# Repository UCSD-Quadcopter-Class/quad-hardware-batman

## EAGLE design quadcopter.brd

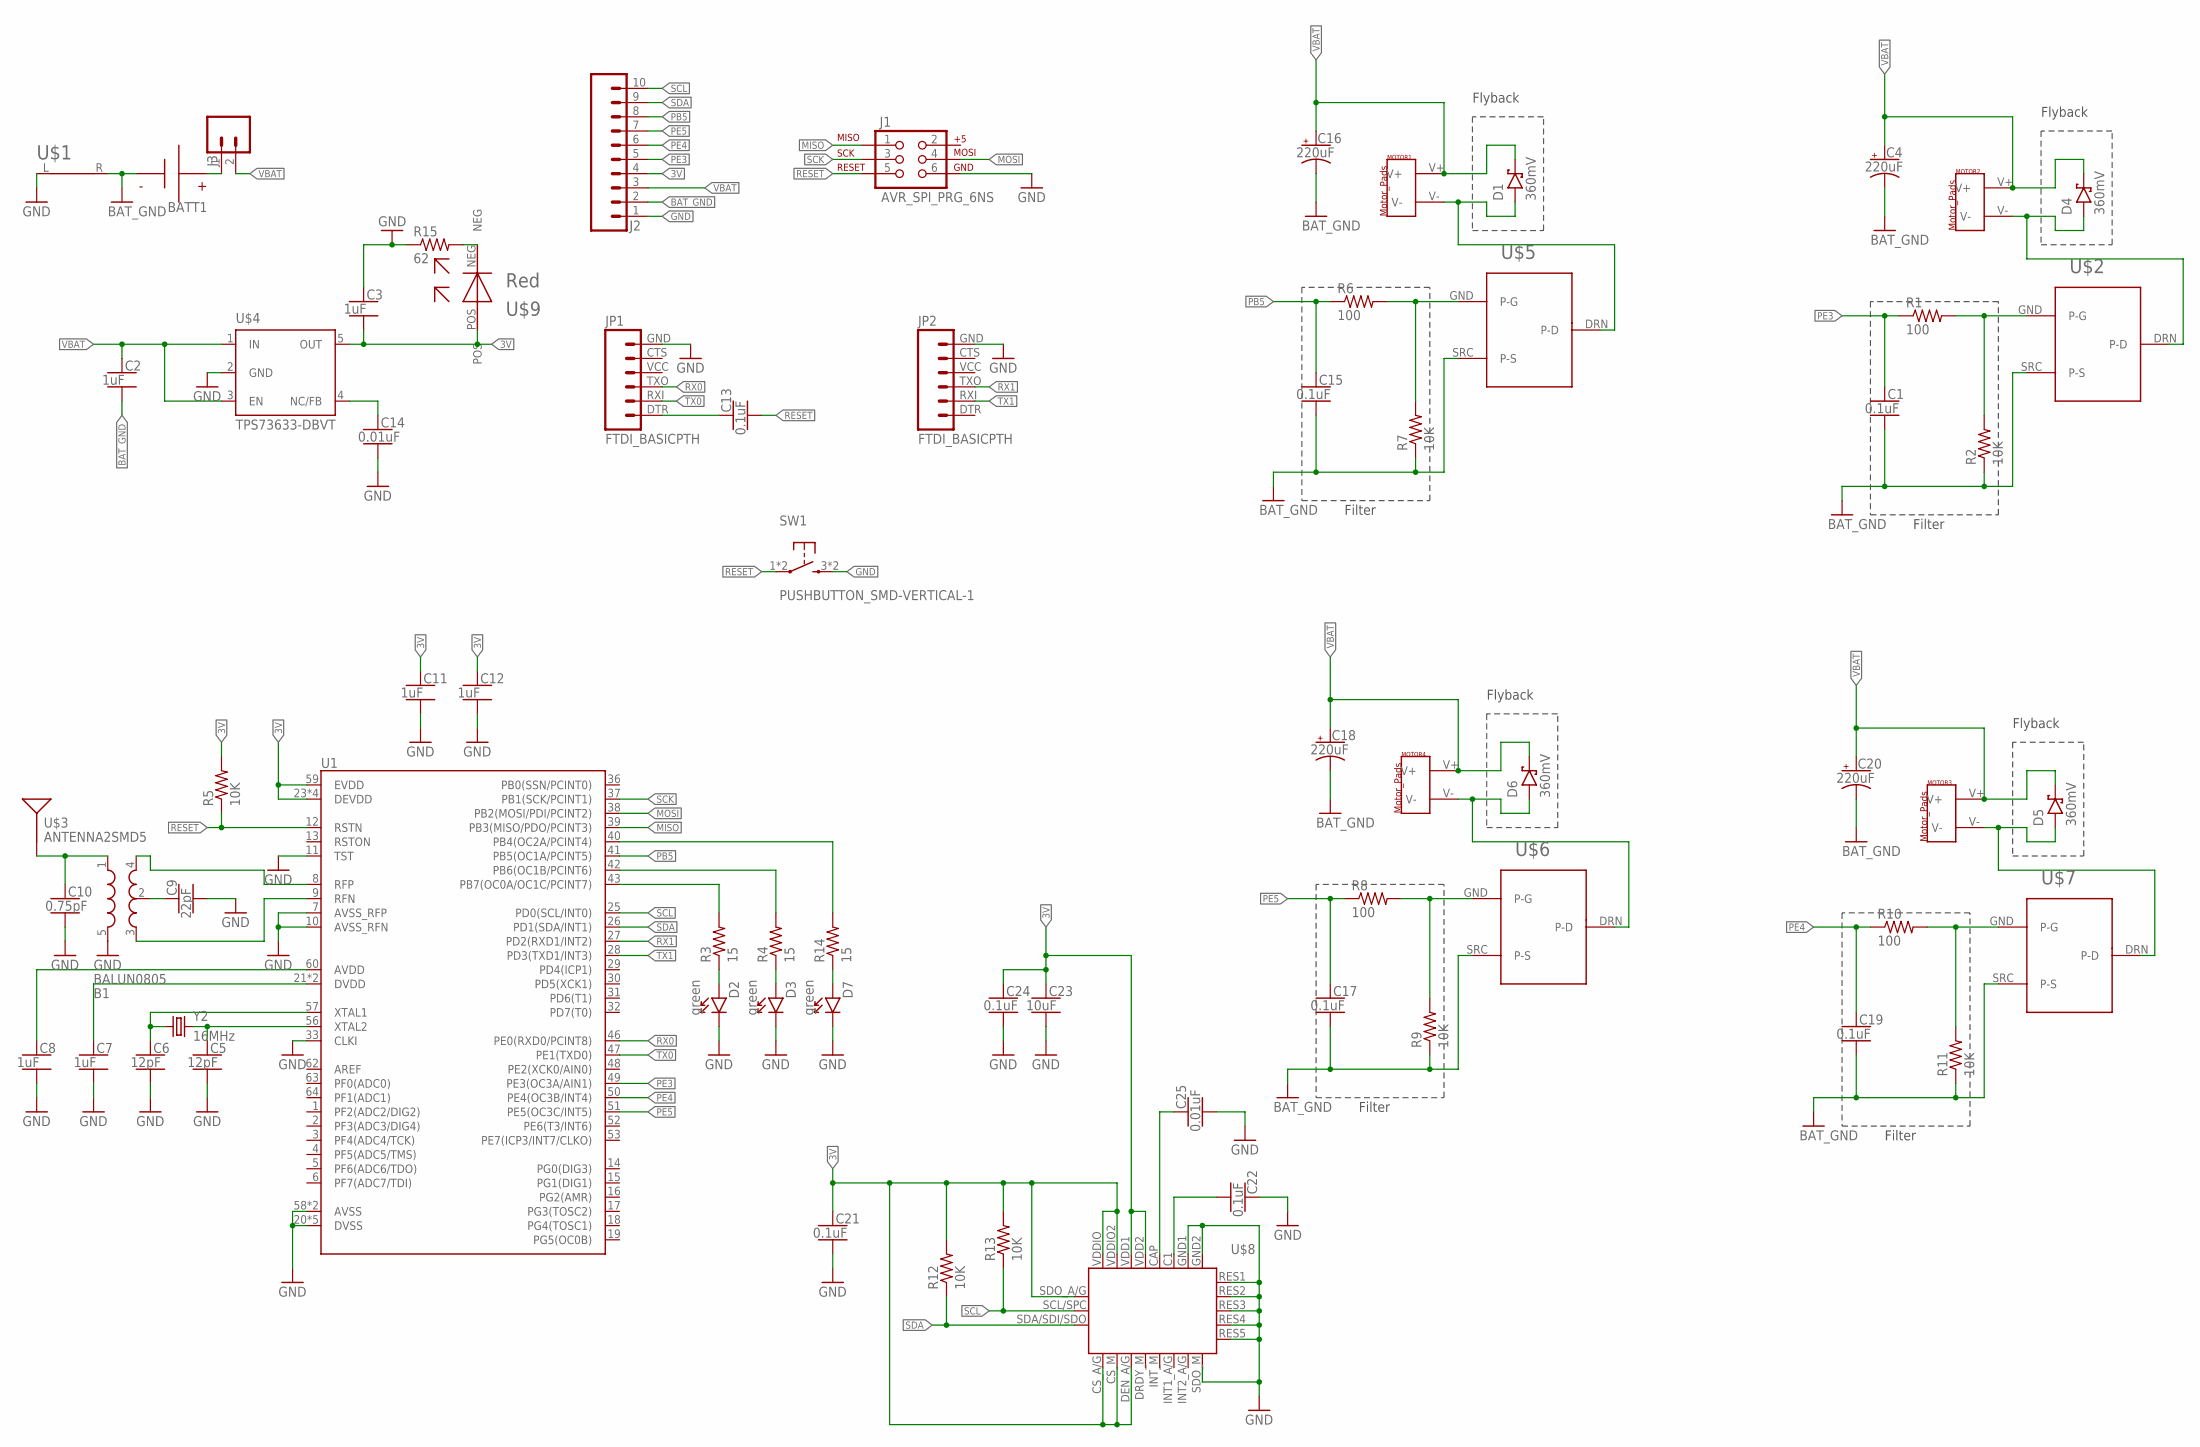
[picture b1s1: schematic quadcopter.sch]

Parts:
B1: BALUN0805; BALUN
BATT1: BATTERY-HUBSAN-W/HOLDER; BATTERY-W/HOLDER-380MAH-HUBSAN
C1, C13, C15, C17, C19, C21, C22, C24: 0.1uF; CAPC2012X140_HS
C2, C3, C7, C8, C11, C12: 1uF; CAPC2012X140_HS
C4, C16, C18, C20: 220uF; CAPMP7343X310_HS
C5, C6: 12pF; CAPC2012X140_HS
C9: 22pF; CAPC2012X140_HS
C10: 0.75pF; CAPC2012X140_HS
C14, C25: 0.01uF; CAPC2012X140_HS
C23: 10uF; CAPC2012X140_HS
D1, D4, D5, D6: 360mV; SOD3716X135_HS
D2, D3, D7: green; LEDSC125X200X120-2_HS
J1: AVR_SPI_PRG_6NS; 2X3-NS
J2: SIP-10_TH-254X10; HDRV10W63P254_10X1_2540X254H838_HS
J3: MALE_HEADER_2POS-2X1-0.1IN; MALE_HEADER_2X1_0.1IN
JP1, JP2: FTDI_BASICPTH; FTDI_BASIC
MOTOR1, MOTOR2, MOTOR3, MOTOR4: MOTOR_PADS
R1, R6, R8, R10: 100; RESC2012X60_HS
R2, R5, R7, R9, R11, R12, R13: 10K; RESC2012X60_HS
R3, R4, R14: 15; RESC2012X60_HS
R15: 62; RESC2012X60_HS
SW1: PUSHBUTTON_SMD-VERTICAL-1; TE_FSM8JSMA_HS
U1: ATMEGA128RFA1; QFN-64
U$1: NET_BRIDGE
U$2, U$5, U$6, U$7: MOSFET_20V
U$3: ANTENNA2SMD5; ANTENNA-CHIP5
U$4: TPS73633-DBVT; SOT23-DBV
U$8: IMU_9AXIS
U$9: Red; RED_LED_0805
Y2: 16MHz; CRYSTAL-SMD-5X3

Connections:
3V: C3.2, C11.1, C12.1, C21.1, C23.1, C24.1, J2.4, R5.2, R12.2, R13.2, U1.23 (DEVDD), U1.34 (DEVDD), U1.44 (DEVDD), U1.54 (DEVDD), U1.59 (EVDD), U$4.5 (OUT), U$8.CS_A/G, U$8.CS_M, U$8.DEN_A/G, U$8.SDO_A/G, U$8.VDD1, U$8.VDD2, U$8.VDDIO (VDDIO1), U$8.VDDIO2, U$9.POS
BAT_GND: BATT1.- (N), C1.2, C2.2, C4.2 (-), C15.2, C16.2 (-), C17.2, C18.2 (-), C19.2, C20.2 (-), J2.2, R2.1, R7.1, R9.1, R11.1, U$1.R, U$2.SRC (P-S), U$5.SRC (P-S), U$6.SRC (P-S), U$7.SRC (P-S)
FILTERED1: R6.2, R7.2, U$5.GND (P-G)
FILTERED2: R1.2, R2.2, U$2.GND (P-G)
FILTERED3: R10.2, R11.2, U$7.GND (P-G)
FILTERED4: R8.2, R9.2, U$6.GND (P-G)
FLYBACK1: D1.A, MOTOR1.V-, U$5.DRN (P-D)
FLYBACK2: D4.A, MOTOR2.V-, U$2.DRN (P-D)
FLYBACK3: D5.A, MOTOR3.V-, U$7.DRN (P-D)
FLYBACK4: D6.A, MOTOR4.V-, U$6.DRN (P-D)
GND: B1.5 (GND), C3.1, C5.2, C6.2, C7.2, C8.2, C9.2, C10.2, C11.2, C12.2, C14.2, C21.2, C22.1, C23.2, C24.2, C25.2, D2.C, D3.C, D7.C, J1.6, J2.1, JP1.GND (6), JP2.GND (6), R15.1, SW1.3 (2), SW1.4 (2), U1.7 (AVSS_RFP), U1.10 (AVSS_RFN), U1.11 (TST), U1.20 (DVSS), U1.24 (DVSS), U1.33 (CLKI), U1.35 (DVSS), U1.45 (DVSS), U1.55 (DVSS), U1.58 (AVSS), U1.61 (AVSS), U$1.L, U$4.2 (GND), U$8.GND1, U$8.GND2, U$8.RES1, U$8.RES2, U$8.RES3, U$8.RES4, U$8.RES5, U$8.SDO_M
MISO: J1.1, U1.39 (PB3(MISO/PDO/PCINT3))
MOSI: J1.4, U1.38 (PB2(MOSI/PDI/PCINT2))
unnamed: C14.1, U$4.4 (NC/FB)
unnamed: D7.A, R14.1
unnamed: D2.A, R3.1
unnamed: C5.1, U1.56 (XTAL2), Y2.3 (2)
unnamed: C6.1, U1.57 (XTAL1), Y2.1
unnamed: D3.A, R4.1
unnamed: C7.1, U1.21 (DVDD), U1.22 (DVDD)
unnamed: C8.1, U1.60 (AVDD)
unnamed: B1.4 (OUT1), U1.8 (RFP)
unnamed: B1.3 (OUT2), U1.9 (RFN)
unnamed: B1.2 (GND), C9.1
unnamed: B1.1 (IN), C10.1, U$3.FEED
unnamed: C13.1, JP1.DTR (1)
unnamed: BATT1.+, J3.1
unnamed: R15.2, U$9.NEG
unnamed: C25.1, U$8.CAP
unnamed: C22.2, U$8.C1
PB4: R14.2, U1.40 (PB4(OC2A/PCINT4))
PB5: C15.1, J2.8, R6.1, U1.41 (PB5(OC1A/PCINT5))
PB6: R4.2, U1.42 (PB6(OC1B/PCINT6))
PB7: R3.2, U1.43 (PB7(OC0A/OC1C/PCINT7))
PE3: C1.1, J2.5, R1.1, U1.49 (PE3(OC3A/AIN1))
PE4: C19.1, J2.6, R10.1, U1.50 (PE4(OC3B/INT4))
PE5: C17.1, J2.7, R8.1, U1.51 (PE5(OC3C/INT5))
RESET: C13.2, J1.5, R5.1, SW1.1, SW1.2 (1), U1.12 (RSTN)
RX0: JP1.TXO (3), U1.46 (PE0(RXD0/PCINT8))
RX1: JP2.TXO (3), U1.27 (PD2(RXD1/INT2))
SCK: J1.3, U1.37 (PB1(SCK/PCINT1))
SCL: J2.10, R13.1, U1.25 (PD0(SCL/INT0)), U$8.SCL/SPC
SDA: J2.9, R12.1, U1.26 (PD1(SDA/INT1)), U$8.SDA/SDI/SDO
TX0: JP1.RXI (2), U1.47 (PE1(TXD0))
TX1: JP2.RXI (2), U1.28 (PD3(TXD1/INT3))
VBAT: C2.1, C4.1 (+), C16.1 (+), C18.1 (+), C20.1 (+), D1.C, D4.C, D5.C, D6.C, J2.3, J3.2, MOTOR1.V+, MOTOR2.V+, MOTOR3.V+, MOTOR4.V+, U$4.1 (IN), U$4.3 (EN)

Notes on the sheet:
Flyback
Filter

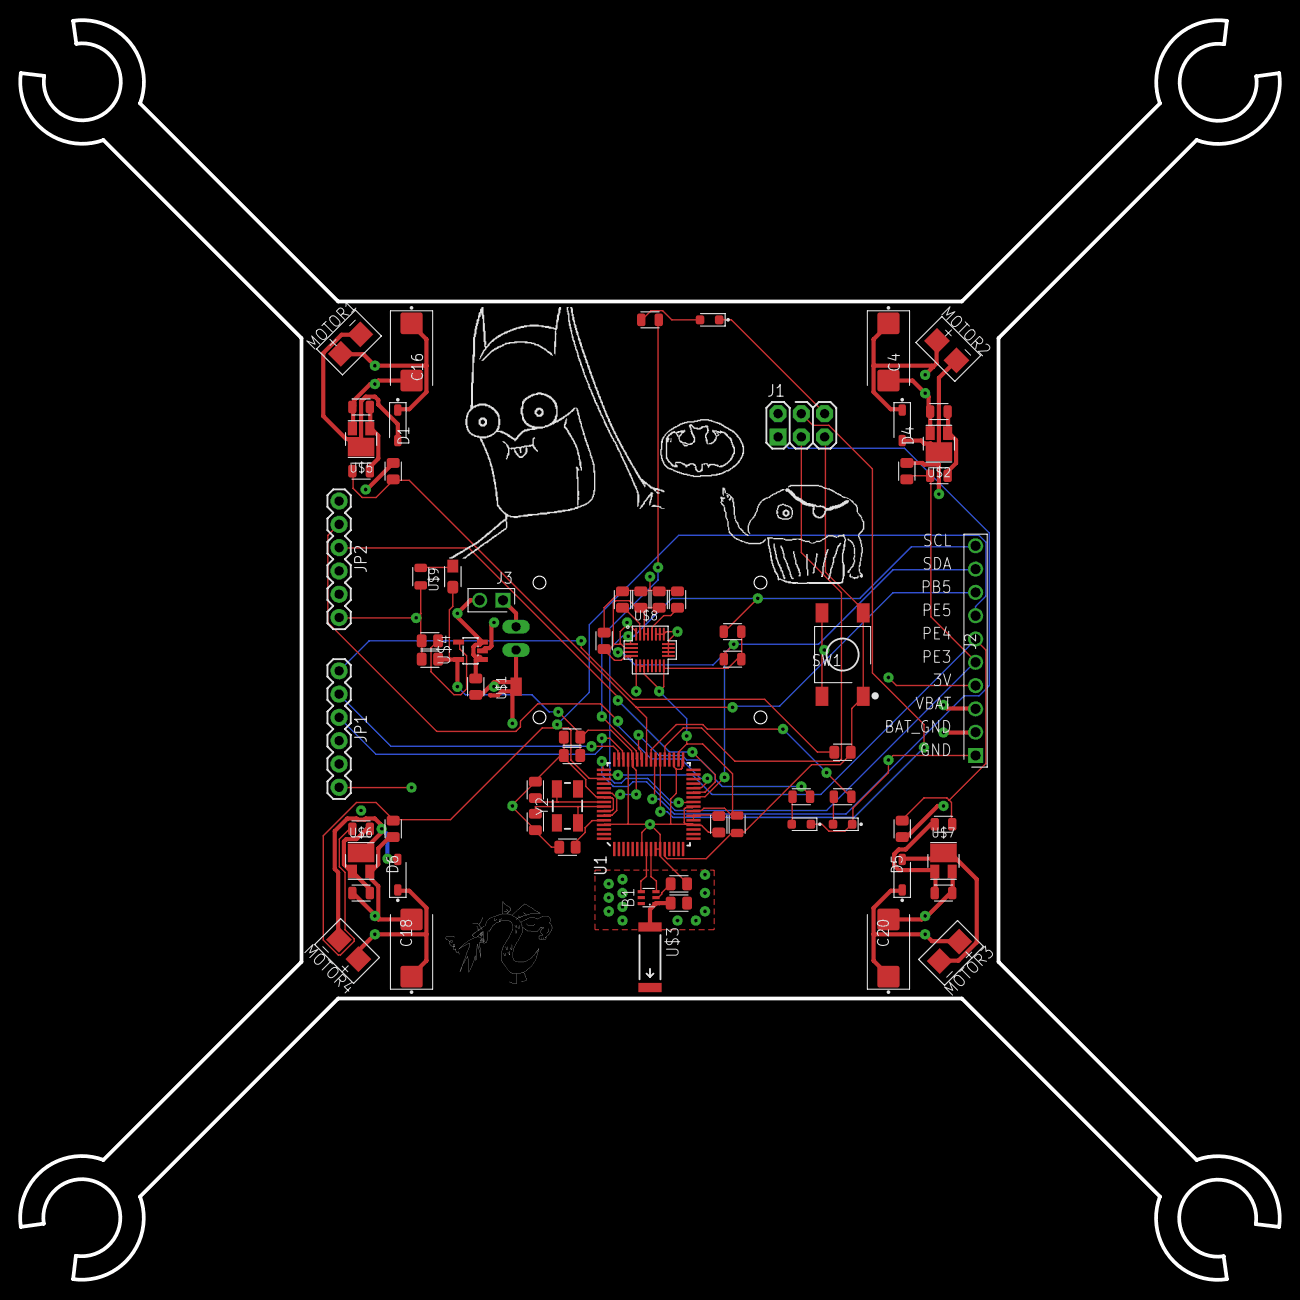
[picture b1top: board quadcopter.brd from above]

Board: 4 copper layers, 137.3 x 137.3 mm, 73 parts (1 on the bottom side), 46 nets.

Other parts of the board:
U$10: DERPY_BATMAN
U$11: MUFFIN_MAN
U$12: TROGDOR

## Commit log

2017-04-18 adding starter files
2017-04-18 Added voltage regulator doc
2017-04-18 Moved/added stuff
2017-04-18 didn't actually make changes to quadcopter.sch, but added the rough schematic of the motor with the updated parts
2017-04-18 Beginning to copy red board design
2017-04-18 added IMU.sch and made an edit to the IMU device in quadparts.lbr
2017-04-18 Added necessary components from red board design
2017-04-18 Added power supply, FTDI and debugging headers, misc. fixes.
2017-04-19 Added battery disconnect, replicated motor controller w/ pwm, misc fixes.
2017-04-19 added IMU to quadcopter
2017-04-19 pinned up IMU
2017-04-20 pushing who am i and final changes to the IMU
2017-04-20 removing IMU schematic file
2017-04-20 adding red led device
2017-04-20 Small fixes for IMU, added PID to who_am_i
2017-04-20 added tag and datasheet for our led
2017-04-20 Added LEDs, correct resistors, and replaced some devices with correct variants.
2017-04-20 final commits for Lab 4
2017-04-20 now, this is really the last commit because there was more to add and now there isn't
2017-04-25 Added review notes and reviewer attribute to devices
2017-04-25 Fixed small issues found from design review
2017-04-25 submitting changes to parts
2017-04-26 Fixed some issues found from review, notably IMU pins
2017-04-27 git after the local repo reset contains quadparts.sch/brd, the new dru, and the modified quadparts.lbr
2017-04-27 instructior review of original schematic
2017-04-28 AO: adding redesigned board with X configuration
2017-04-29 added the ground and power planes to the board as well as the Ground Shield/Faraday cage to the antenna but may need review
2017-04-30 Fixed small issues in schematic, worked on board layout (antenna and pour connections mostly)
2017-05-01 Board optimizations, focusing on IMU and making space for the autorouter.
2017-05-02 Optimized clock and antenna placement, fixed net bridge, misc. optimizations.
2017-05-02 Board fully routed
2017-05-04 Added board design review docs
2017-05-04 Removed filter/flyback labels in schematic, refined placement of many board components
2017-05-05 Fixed motor holder and arm dimensions (now fits within bounding box
2017-05-06 Manually routed crystal, minor optimizations
2017-05-06 Routed board
2017-05-08 Repositioned battery holder and voltage regulator
2017-05-09 Minor tweaks, added CAM folder
2017-05-09 Adding notes on the noise problem and solution.
2017-05-09 Ready to be routed
2017-05-09 Routed board with CAM files
2017-05-10 Updated CAM files
2017-05-11 Added logos
2017-05-11 commiting new CAM files and new board logos
2017-05-11 Board ready to be routed with new DRU file
2017-05-11 new cam files and rerouted board and stuff
2017-05-11 Deleted old cam folder
2017-05-11 Ripped up everything, manually placed some vias, ready to be routed
2017-05-11 Changed antenna vias, added routes from balun
2017-05-11 Manually routed crystal, fixed motor driver filters.
2017-05-11 Routed board, CAM files
2017-05-11 swanson review
2017-05-13 Fixed issues found by Swanson's review, board ready to be auto-routed
2017-05-14 More schematic comments from swanson
2017-05-14 Fixed additional issues found by Swanson in schematic
2017-05-14 Auto-routed board
2017-05-15 Fixed small airwire
